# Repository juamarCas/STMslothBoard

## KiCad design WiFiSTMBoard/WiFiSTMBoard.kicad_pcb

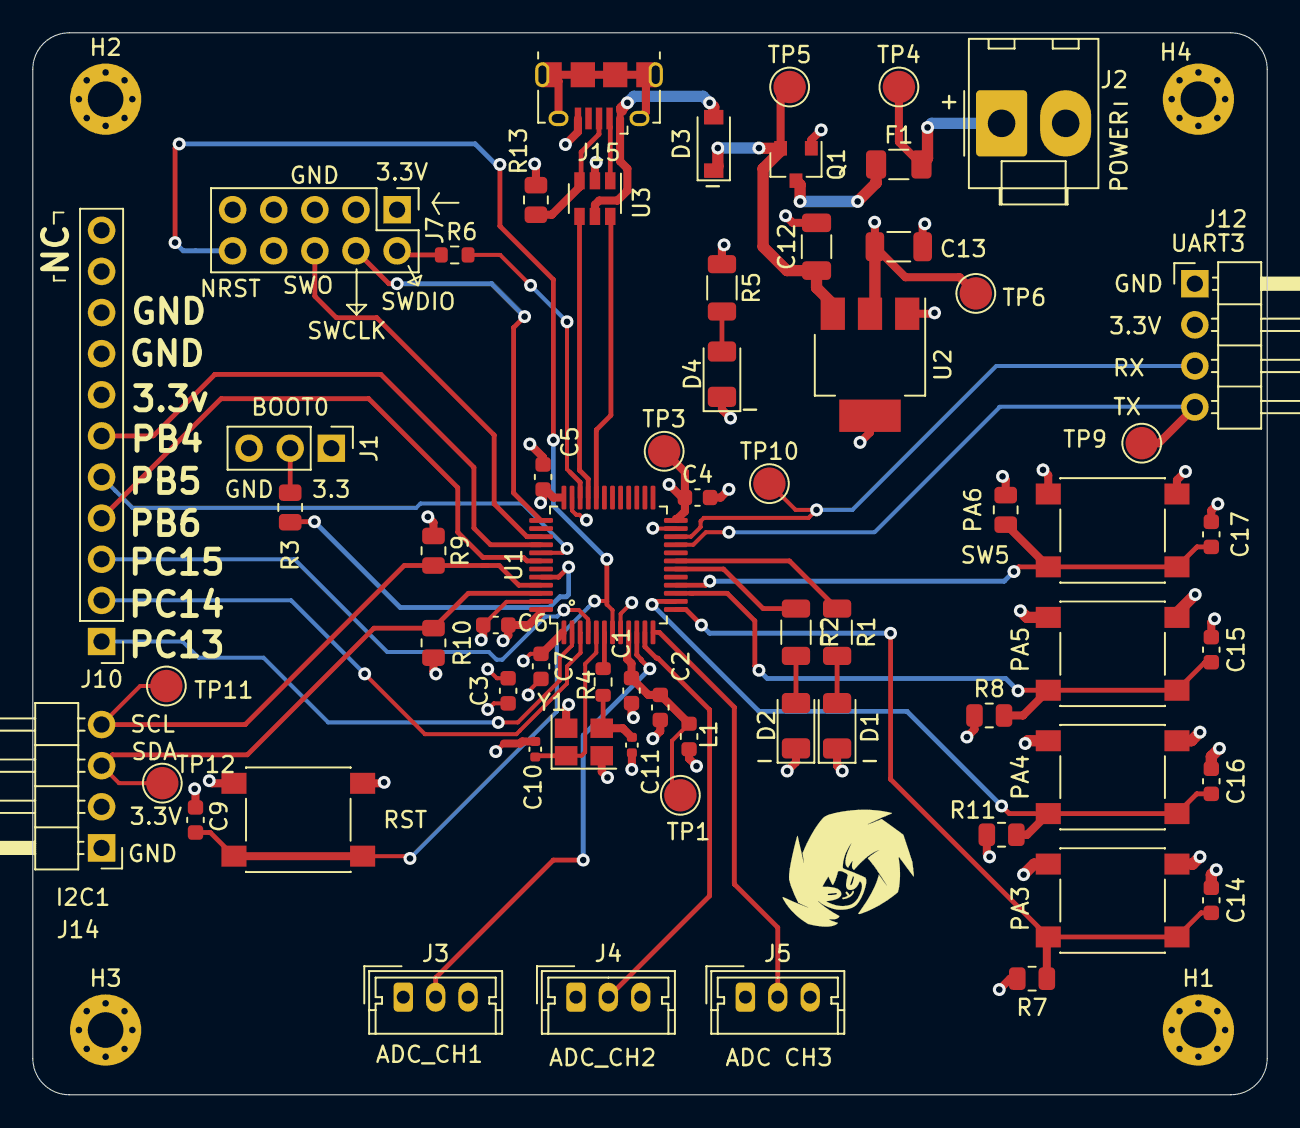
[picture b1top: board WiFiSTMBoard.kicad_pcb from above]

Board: 4 copper layers, 76.2 x 65.6 mm, 68 parts (0 on the bottom side), 43 nets.

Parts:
C1: 1n; C_0603_1608Metric
C2, C14, C15, C16, C17: 10n; C_0603_1608Metric
C3: 4.7u; C_0603_1608Metric
C4, C5, C6, C7, C9: 100n; C_0603_1608Metric
C10, C11: 12p; C_0402_1005Metric
C12, C13: 10u; C_1206_3216Metric
D1, D2, D4: LED_Small; LED_1206_3216Metric
D3: D_Schottky_Small; D_SOD-123
F1: 500 mA; Fuse_1206_3216Metric
H1, H2, H3, H4: MountingHole_Pad; MountingHole_2.2mm_M2_Pad_Via
J1: Conn_01x03_Male; PinHeader_1x03_P2.54mm_Vertical
J2: Conn_01x02_Male; Molex_KK-396_A-41791-0002_1x02_P3.96mm_Vertical
J3, J4, J5: Conn_01x03_Male; Molex_Micro-Latch_53253-0370_1x03_P2.00mm_Vertical
J7: SWD; PinHeader_2x05_P2.54mm_Vertical
J10: Conn_01x11_Male; PinHeader_1x11_P2.54mm_Vertical
J12, J14: Conn_01x04_Male; PinHeader_1x04_P2.54mm_Horizontal
J15: USB_B_Micro; USB_Micro-B_Amphenol_10118194_Horizontal
L1: 39n; L_0603_1608Metric
PA3: PB12; SW_Push_1P1T_NO_6x6mm_H9.5mm
PA4: PB13; SW_Push_1P1T_NO_6x6mm_H9.5mm
PA5: PB14; SW_Push_1P1T_NO_6x6mm_H9.5mm
PA6: 10k; R_0805_2012Metric
Q1: AO3401A; SOT-23
R1, R2, R5: 1k; R_1206_3216Metric
R3, R7, R8, R11: 10k; R_0805_2012Metric
R4: 820; R_0603_1608Metric
R6: 22; R_0603_1608Metric
R9, R10: 4.7k; R_0805_2012Metric
R13: 1.5k; R_0805_2012Metric
RST: SW_Push_Dual_x2; SW_Push_1P1T_NO_6x6mm_H9.5mm
SW5: PB15; SW_Push_1P1T_NO_6x6mm_H9.5mm
TP1, TP3: TestPoint; TestPoint_Pad_D2.0mm
TP4, TP5, TP6: TP; TestPoint_Pad_D2.0mm
TP9: TX3_TP; TestPoint_Pad_D2.0mm
TP10: RX3_TP; TestPoint_Pad_D2.0mm
TP11: SCL_TP; TestPoint_Pad_D2.0mm
TP12: SDA_TP; TestPoint_Pad_D2.0mm
U1: STM32F302C8Tx; LQFP-48_7x7mm_P0.5mm
U2: AMS1117-3.3; SOT-223-3_TabPin2
U3: USBLC6-2SC6; SOT-23-6
Y1: 16MHz; Crystal_SMD_3225-4Pin_3.2x2.5mm

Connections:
+3.3VA: C1.1, C2.1, L1.2, TP1.1, U1.9
+3V3: C3.1, C4.1, C5.1, C6.1, C7.1, C13.1, J1.1, J3.3, J4.3, J5.3, J7.1, J10.7, J12.2, J14.2, L1.1, PA6.1, R5.1, R7.1, R8.1, R9.1, R10.1, R11.1, R13.1, TP3.1, TP6.1, U1.1, U1.24, U1.36, U1.48, U2.2
+5V: D3.2, J15.1, U3.5
ADC1_CH1: J3.2, U1.10
ADC1_CH2: J4.2, U1.11
ADC1_CH3: J5.2, U1.12
BOOT0: R3.2, U1.44
GND: C1.2, C2.2, C3.2, C4.2, C5.2, C6.2, C7.2, C9.1, C10.2, C11.2, C12.2, C13.2, C14.2, C15.2, C16.2, C17.2, D1.1, D2.1, D4.1, H1.1, H2.1, H3.1, H4.1, J1.3, J2.2, J3.1, J4.1, J5.1, J7.3, J7.5, J7.9, J10.8, J10.9, J12.1, J14.1, J15.5, PA3.2, PA4.2, PA5.2, Q1.1, RST.2, SW5.2, U1.8, U1.23, U1.35, U1.47, U2.1, U3.2, Y1.2, Y1.4
LED_1: R1.1, U1.19
LED_2: R2.1, U1.18
NRST: C9.2, J7.10, RST.1, U1.7
unnamed: C11.1, R4.2, Y1.3
unnamed: C12.1, D3.1, Q1.2, TP5.1, U2.3
unnamed: D1.2, R1.2
unnamed: D2.2, R2.2
unnamed: D4.2, R5.2
unnamed: F1.1, Q1.3
unnamed: J1.2, R3.1
unnamed: J7.2, R6.1
OSC_IN: C10.1, U1.5, Y1.1
OSC_OUT: R4.1, U1.6
PA3_BTN: C14.1, PA3.1, R7.2, U1.13
PA4_BTN: C16.1, PA4.1, R11.2, U1.14
PA5_BTN: C15.1, PA5.1, R8.2, U1.15
PA6_BTN: C17.1, PA6.2, SW5.1, U1.16
PB4_GPIO: J10.6, U1.40
PB5_GPIO: J10.5, U1.41
PB6_GPIO: J10.4, U1.42
PC13: J10.1, U1.2
PC14: J10.2, U1.3
PC15: J10.3, U1.4
SCL: J14.4, R9.2, TP11.1, U1.45
SDA: J14.3, R10.2, TP12.1, U1.46
SWCLK: J7.4, U1.37
SWDIO: R6.2, U1.34
SWO: J7.6, U1.39
USART3_RX: J12.3, TP10.1, U1.22
USART3_TX: J12.4, TP9.1, U1.21
USB_CONN_DM: J15.2, U3.1
USB_CONN_DP: J15.3, R13.2, U3.3
USB_DM: U1.32, U3.6
USB_DP: U1.33, U3.4
VCC: F1.2, J2.1, TP4.1

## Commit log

2021-11-13 initial
2021-11-13 added input
2021-11-14 added esp8266
2021-11-14 removed esp8266 diagram, added ch3040 diagram
2021-11-15 finished serial circuit
2021-11-16 starting PCB layout
